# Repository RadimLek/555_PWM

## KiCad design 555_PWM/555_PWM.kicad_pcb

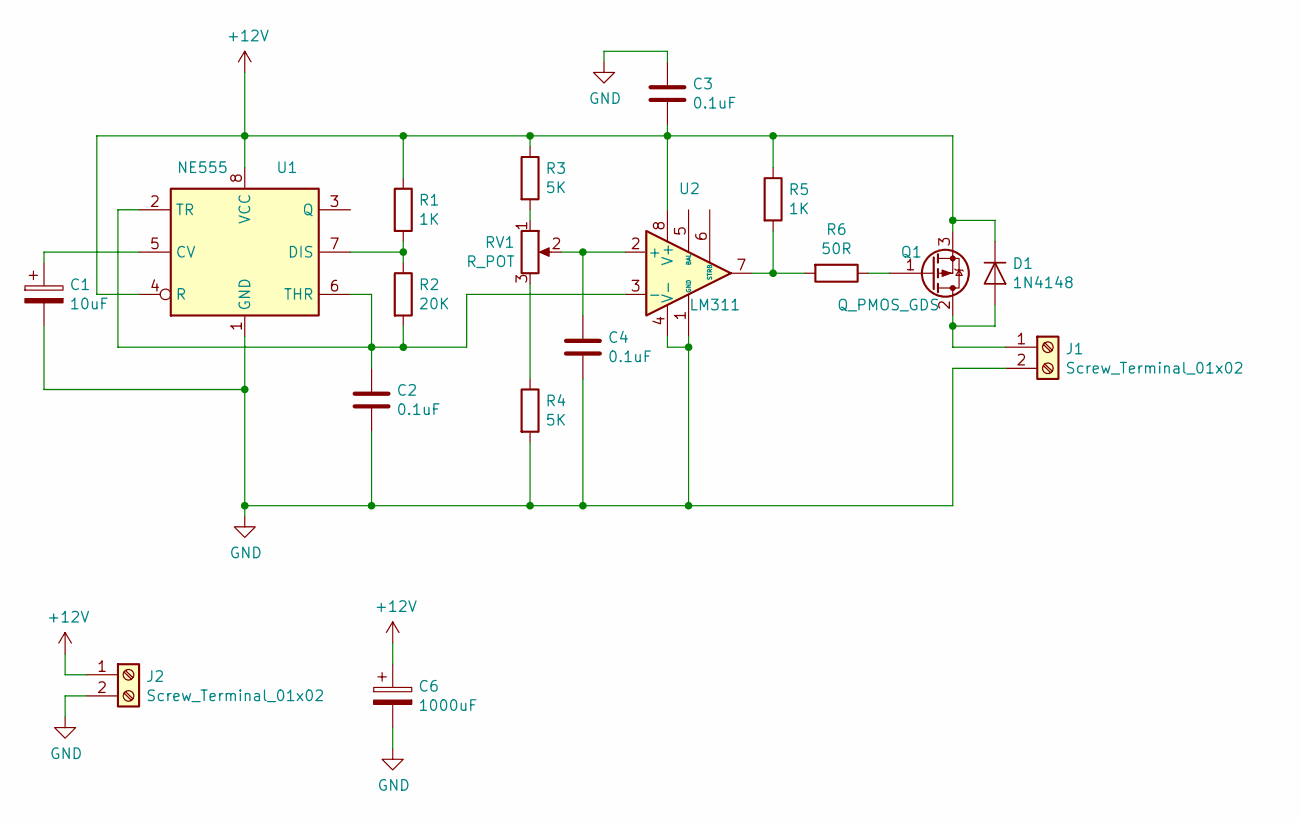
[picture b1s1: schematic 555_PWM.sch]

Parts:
C1: 10uF; CP_Radial_D5.0mm_P2.50mm
C2, C3, C4: 0.1uF; C_Disc_D4.3mm_W1.9mm_P5.00mm
C6: 1000uF; CP_Radial_D10.0mm_P5.00mm
D1: 1N4148; D_DO-35_SOD27_P10.16mm_Horizontal
J1, J2: Screw_Terminal_01x02; TerminalBlock_bornier-2_P5.08mm
Q1: Q_PMOS_GDS; TO-220-3_Vertical
R1, R5: 1K; R_1206_3216Metric_Pad1.42x1.75mm_HandSolder
R2: 20K; R_1206_3216Metric_Pad1.42x1.75mm_HandSolder
R3, R4: 5K; R_1206_3216Metric_Pad1.42x1.75mm_HandSolder
R6: 50R; R_1206_3216Metric_Pad1.42x1.75mm_HandSolder
RV1: R_POT; PinHeader_1x03_P2.54mm_Vertical
U1: NE555; DIP-8_W7.62mm
U2: LM311; DIP-8_W7.62mm

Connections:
+12V: C3.2, C6.1, D1.1 (K), J2.1, Q1.3 (S), R1.1, R3.1, R5.1, U1.4 (R), U1.8 (VCC), U2.8 (V+)
GND: C1.2, C2.2, C3.1, C4.2, C6.2, J1.2, J2.2, R4.2, U1.1 (GND), U2.1 (GND), U2.4 (V-)
unnamed: C1.1, U1.5 (CV)
unnamed: C2.1, R2.2, U1.2 (TR), U1.6 (THR), U2.3 (-)
unnamed: C4.1, RV1.2, U2.2 (+)
unnamed: D1.2 (A), J1.1, Q1.2 (D)
unnamed: Q1.1 (G), R6.1
unnamed: R1.2, R2.1, U1.7 (DIS)
unnamed: R3.2, RV1.1
unnamed: R4.1, RV1.3
unnamed: R5.2, R6.2, U2.7

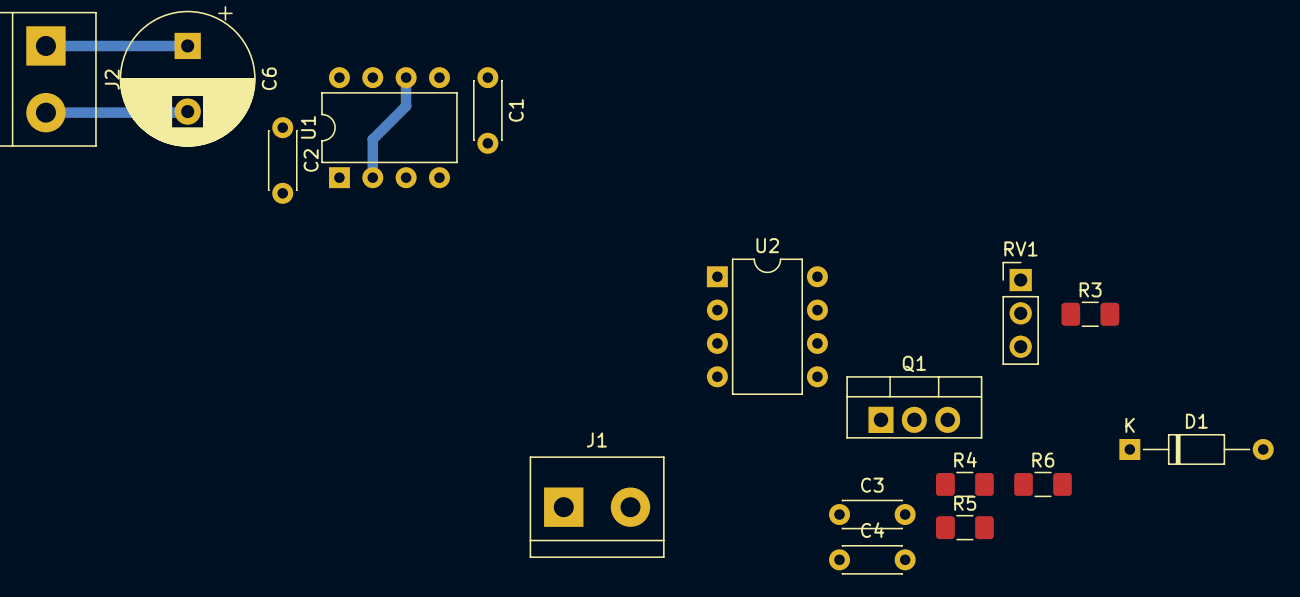
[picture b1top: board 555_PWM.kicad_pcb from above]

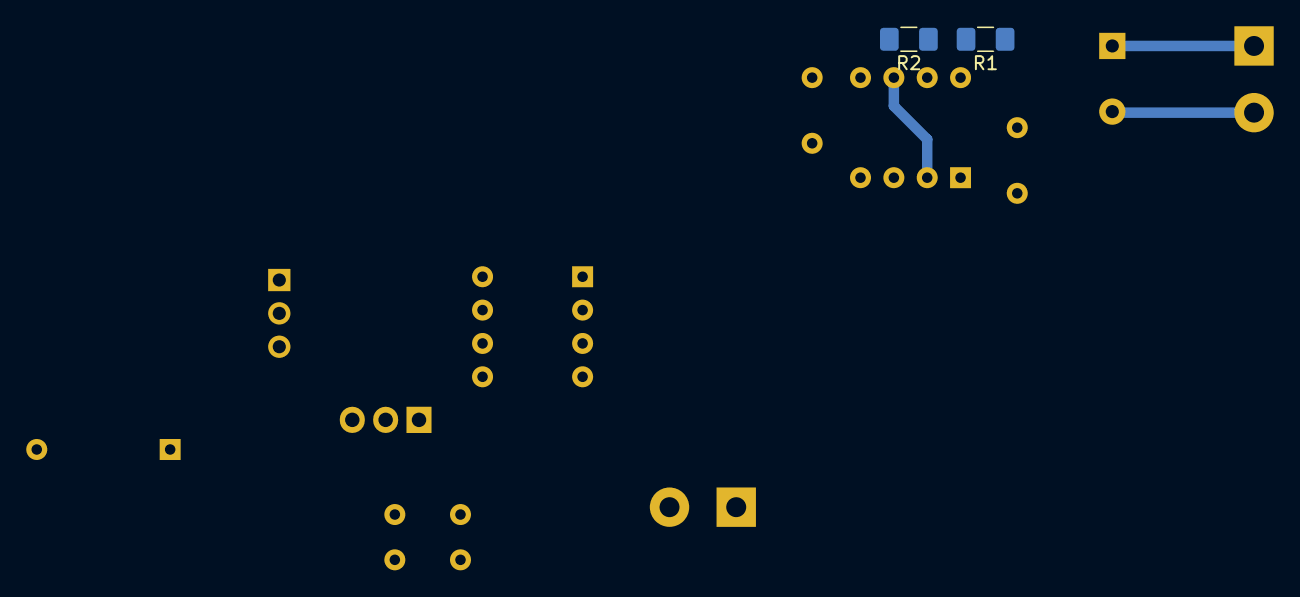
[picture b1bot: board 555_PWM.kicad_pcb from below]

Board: 2 copper layers, 18 parts (2 on the bottom side), 11 nets.

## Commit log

2020-02-27 Developing PWM controller
2020-02-27 накидал схему
2020-02-27 начал трассировку
